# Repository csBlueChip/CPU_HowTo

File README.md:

Ideally:
* Grab a copy of Notepad++
* Load the provided language file
* Read the HowTo

Sub-optimally:
* Read the HowTo without the syntax highlighing

Alternatively:
* Port the language file to your favourite text editor
* `~~~ (  SECTION HEADING  ) =====`<br/>
`~-~ SUBSECTION HEADING ~-~ `<br/>
`(o) DIAGRAM TITLE`<br/>
`! ASCII Art`<br/>
`` `CODE` ``<br/>
`"QUOTED STRING"`<br/>
`<~ SPOILER ~>`<br/>
`{NAME}`<br/>
`!!!ALERT!!!`<br/>

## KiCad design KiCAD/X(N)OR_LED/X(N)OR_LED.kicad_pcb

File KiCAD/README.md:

&nbsp;&nbsp;&nbsp;<br/>
&nbsp;&nbsp;&nbsp;<br/>

&nbsp;&nbsp;&nbsp;<br/>

&nbsp;&nbsp;&nbsp;<br/>
&nbsp;&nbsp;&nbsp;<br/>

&nbsp;&nbsp;&nbsp;<br/>

&nbsp;&nbsp;&nbsp;<br/>
&nbsp;&nbsp;&nbsp;<br/>
&nbsp;&nbsp;&nbsp;<br/>
&nbsp;&nbsp;&nbsp;<br/>

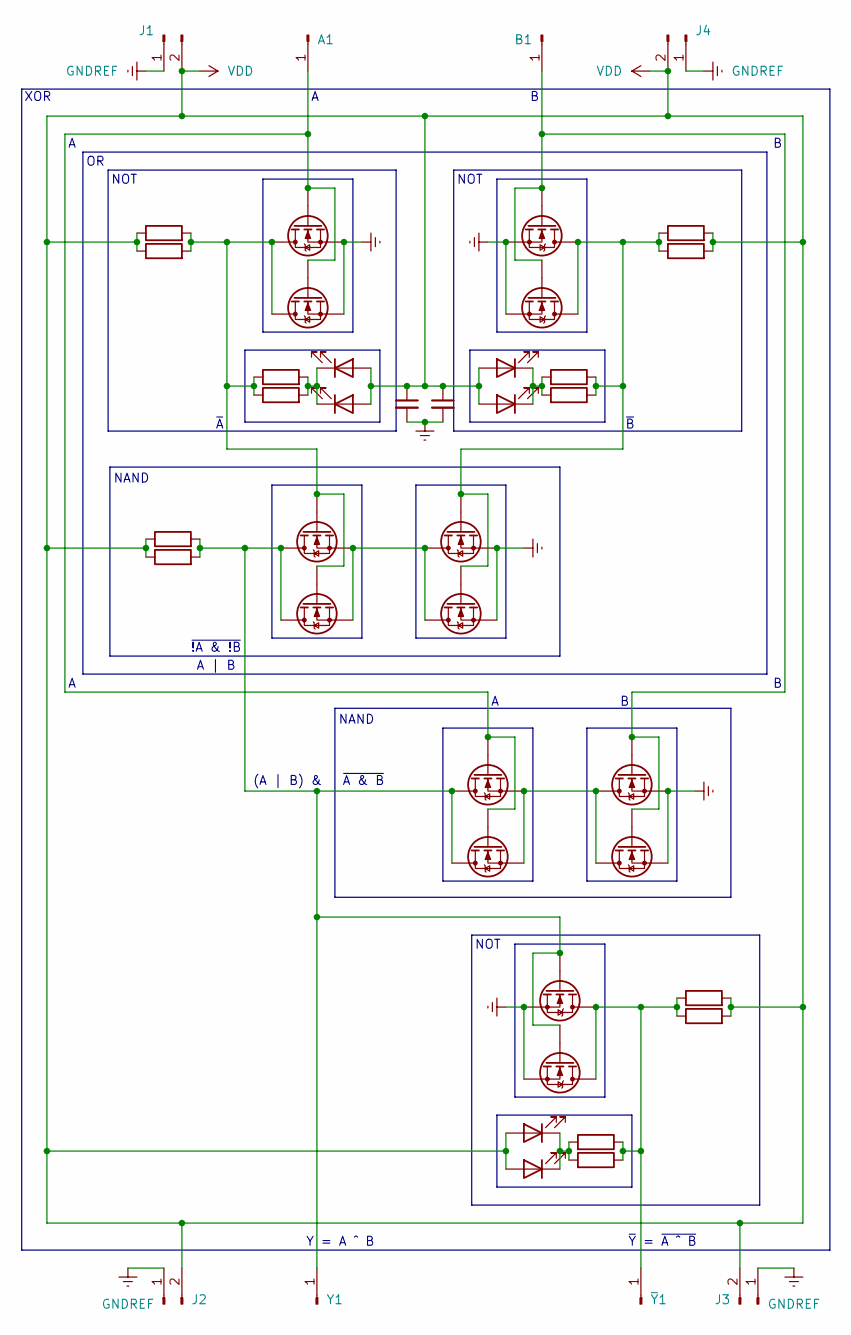
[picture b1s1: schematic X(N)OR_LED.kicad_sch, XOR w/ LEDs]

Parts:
A1: Conn_01x01_Pin; PinHeader_1x01_P2.54mm_Vertical
B1: Conn_01x01_Pin; PinHeader_1x01_P2.54mm_Vertical
C1: C_Small; C_Disc_D3.0mm_W2.0mm_P2.50mm
C2: C_Small; C_1206_3216Metric_Pad1.33x1.80mm_HandSolder
D1, D2, D3: LED; LED_D1.8mm_W3.3mm_H2.4mm
D11, D12, D13: LED; LED_1206_3216Metric
J1, J2, J3, J4: Conn_01x02_Pin; PinSocket_1x02_P2.54mm_Vertical
Q1, Q2, Q3, Q4, Q5, Q6, Q7: 2N7000; TO-92_Inline
Q11, Q12, Q13, Q14, Q15, Q16, Q17: 2N7000; SOT-23
R1, R2, R3, R4, R5, R6, R7: R; R_Axial_DIN0207_L6.3mm_D2.5mm_P10.16mm_Horizontal
R11, R12, R13, R14, R15, R16, R17: R; R_1206_3216Metric
Y1: Conn_01x01_Pin; PinHeader_1x01_P2.54mm_Vertical
~{Y}1: Conn_01x01_Pin; PinHeader_1x01_P2.54mm_Vertical

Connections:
GNDREF: C1.2, C2.2, J1.1, J2.1, J3.1, J4.1, Q1.1 (S), Q2.1 (S), Q4.1 (S), Q6.1 (S), Q7.1 (S), Q11.1 (S), Q12.1 (S), Q14.1 (S), Q16.1 (S), Q17.1 (S)
unnamed: A1.1, Q1.2 (G), Q5.2 (G), Q11.2 (G), Q15.2 (G)
unnamed: B1.1, Q2.2 (G), Q6.2 (G), Q12.2 (G), Q16.2 (G)
unnamed: D1.1 (K), D11.1 (K), R3.2, R13.2
unnamed: D2.1 (K), D12.1 (K), R4.2, R14.2
unnamed: D3.1 (K), D13.1 (K), R7.2, R17.2
unnamed: Q1.3 (D), Q3.2 (G), Q11.3 (D), Q13.2 (G), R1.2, R3.1, R11.2, R13.1
unnamed: Q2.3 (D), Q4.2 (G), Q12.3 (D), Q14.2 (G), R2.1, R4.1, R12.1, R14.1
unnamed: Q3.3 (D), Q5.3 (D), Q7.2 (G), Q13.3 (D), Q15.3 (D), Q17.2 (G), R5.2, R15.2, Y1.1
unnamed: Q3.1 (S), Q4.3 (D), Q13.1 (S), Q14.3 (D)
unnamed: Q5.1 (S), Q6.3 (D), Q15.1 (S), Q16.3 (D)
unnamed: Q7.3 (D), Q17.3 (D), R6.1, R7.1, R16.1, R17.1, ~{Y}1.1
VDD: C1.1, C2.1, D1.2 (A), D2.2 (A), D3.2 (A), D11.2 (A), D12.2 (A), D13.2 (A), J1.2, J2.2, J3.2, J4.2, R1.1, R2.2, R5.1, R6.2, R11.1, R12.2, R15.1, R16.2

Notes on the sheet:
NOT
~{Y} = ~{A ^ B}
XOR
~{A}
~{!A & !B}
A | B
NAND
Y = A ^ B
~{B}
(A | B) & ~{A & B}

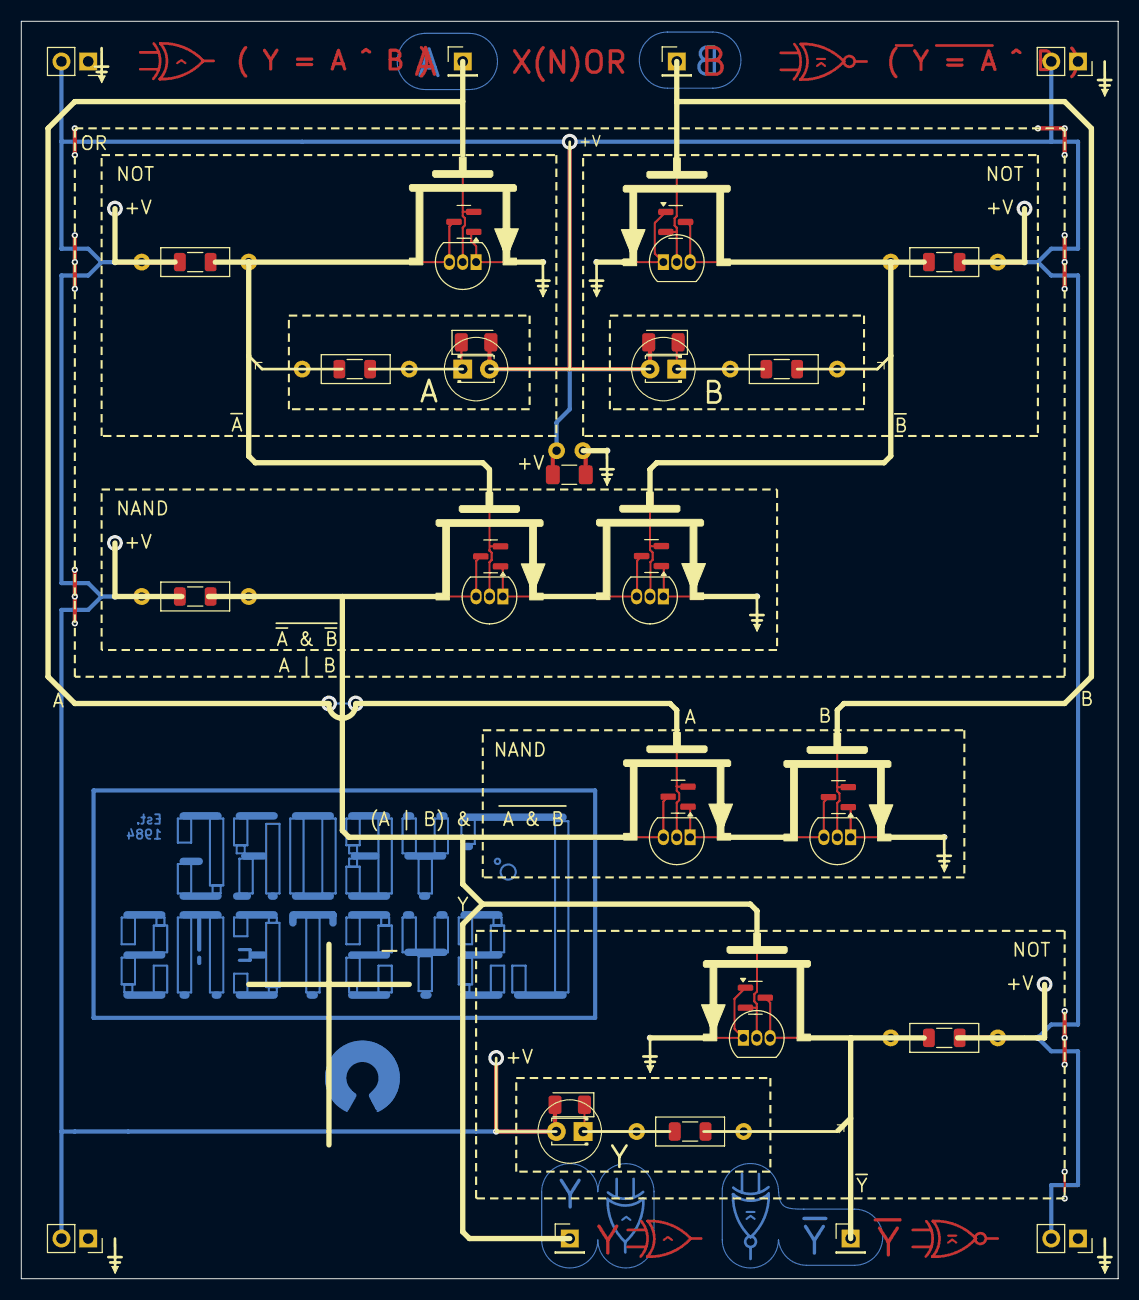
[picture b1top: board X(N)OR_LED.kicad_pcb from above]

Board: 2 copper layers, 104.1 x 119.4 mm, 43 parts (0 on the bottom side), 13 nets.

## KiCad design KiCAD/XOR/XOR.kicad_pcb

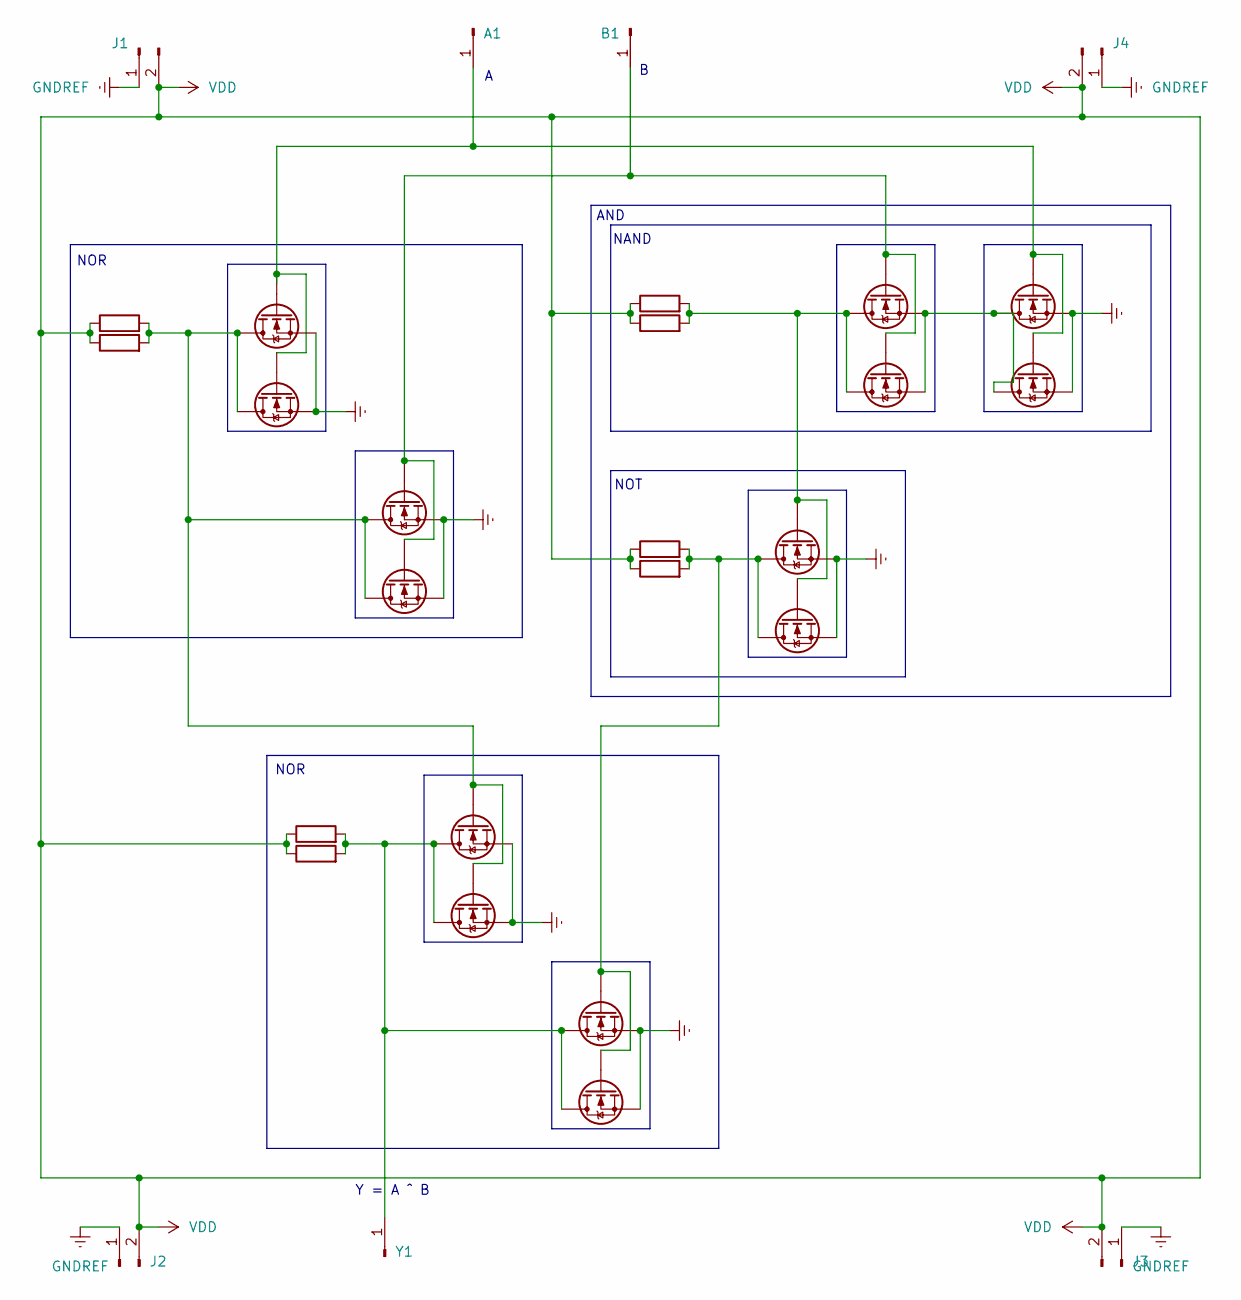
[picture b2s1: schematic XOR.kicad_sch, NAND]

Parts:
A1: Conn_01x01_Pin; PinHeader_1x01_P2.54mm_Vertical
B1: Conn_01x01_Pin; PinHeader_1x01_P2.54mm_Vertical
J1, J2, J3, J4: Conn_01x02_Pin; PinSocket_1x02_P2.54mm_Vertical
Q5, Q6, Q7, Q8, Q9, Q10, Q11: 2N7000; TO-92_Inline
Q15, Q16, Q17, Q18, Q19, Q20, Q21: 2N7000; SOT-23
R6, R7, R8, R9: R; R_Axial_DIN0207_L6.3mm_D2.5mm_P10.16mm_Horizontal
R16, R17, R18, R19: R; R_1206_3216Metric
Y1: Conn_01x01_Pin; PinHeader_1x01_P2.54mm_Vertical

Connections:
GNDREF: J1.1, J2.1, J3.1, J4.1, Q5.1 (S), Q6.1 (S), Q7.1 (S), Q8.1 (S), Q10.1 (S), Q11.1 (S), Q15.1 (S), Q16.1 (S), Q17.1 (S), Q18.1 (S), Q20.1 (S), Q21.1 (S)
unnamed: A1.1, Q5.2 (G), Q10.2 (G), Q15.2 (G), Q20.2 (G)
unnamed: B1.1, Q6.2 (G), Q9.2 (G), Q16.2 (G), Q19.2 (G)
unnamed: Q9.1 (S), Q10.3 (D), Q19.1 (S), Q20.3 (D)
unnamed: Q8.2 (G), Q11.3 (D), Q18.2 (G), Q21.3 (D), R9.2, R19.2
unnamed: Q9.3 (D), Q11.2 (G), Q19.3 (D), Q21.2 (G), R8.2, R18.2
unnamed: Q5.3 (D), Q6.3 (D), Q7.2 (G), Q15.3 (D), Q16.3 (D), Q17.2 (G), R6.2, R16.2
unnamed: Q7.3 (D), Q8.3 (D), Q17.3 (D), Q18.3 (D), R7.2, R17.2, Y1.1
VDD: J1.2, J2.2, J3.2, J4.2, R6.1, R7.1, R8.1, R9.1, R16.1, R17.1, R18.1, R19.1

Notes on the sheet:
NOR
AND
NAND
Y = A ^ B
NOT

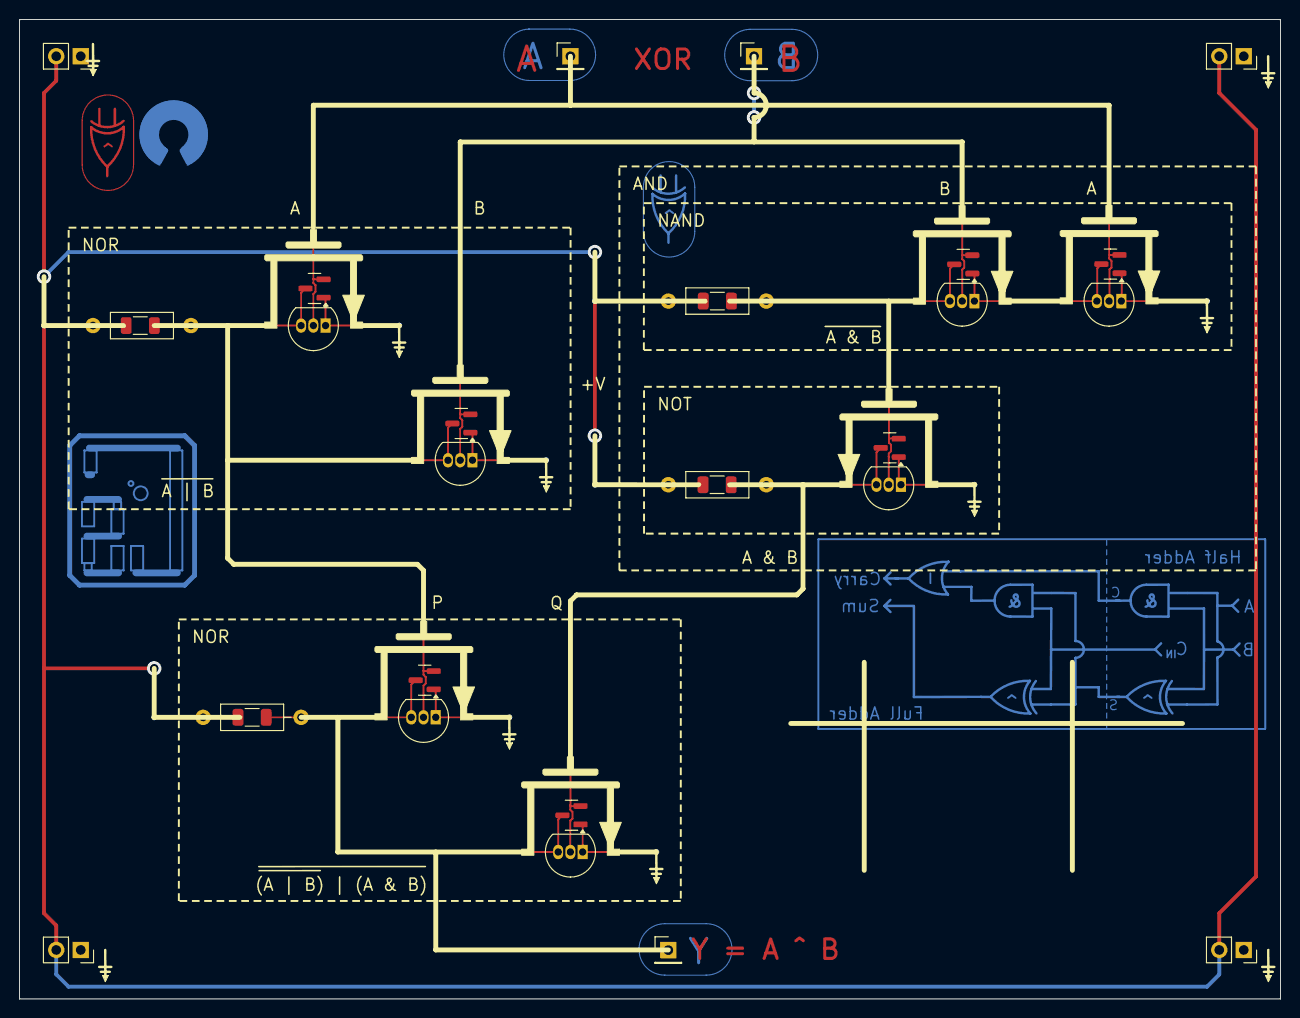
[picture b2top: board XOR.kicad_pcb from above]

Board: 2 copper layers, 130.8 x 101.6 mm, 29 parts (0 on the bottom side), 9 nets.

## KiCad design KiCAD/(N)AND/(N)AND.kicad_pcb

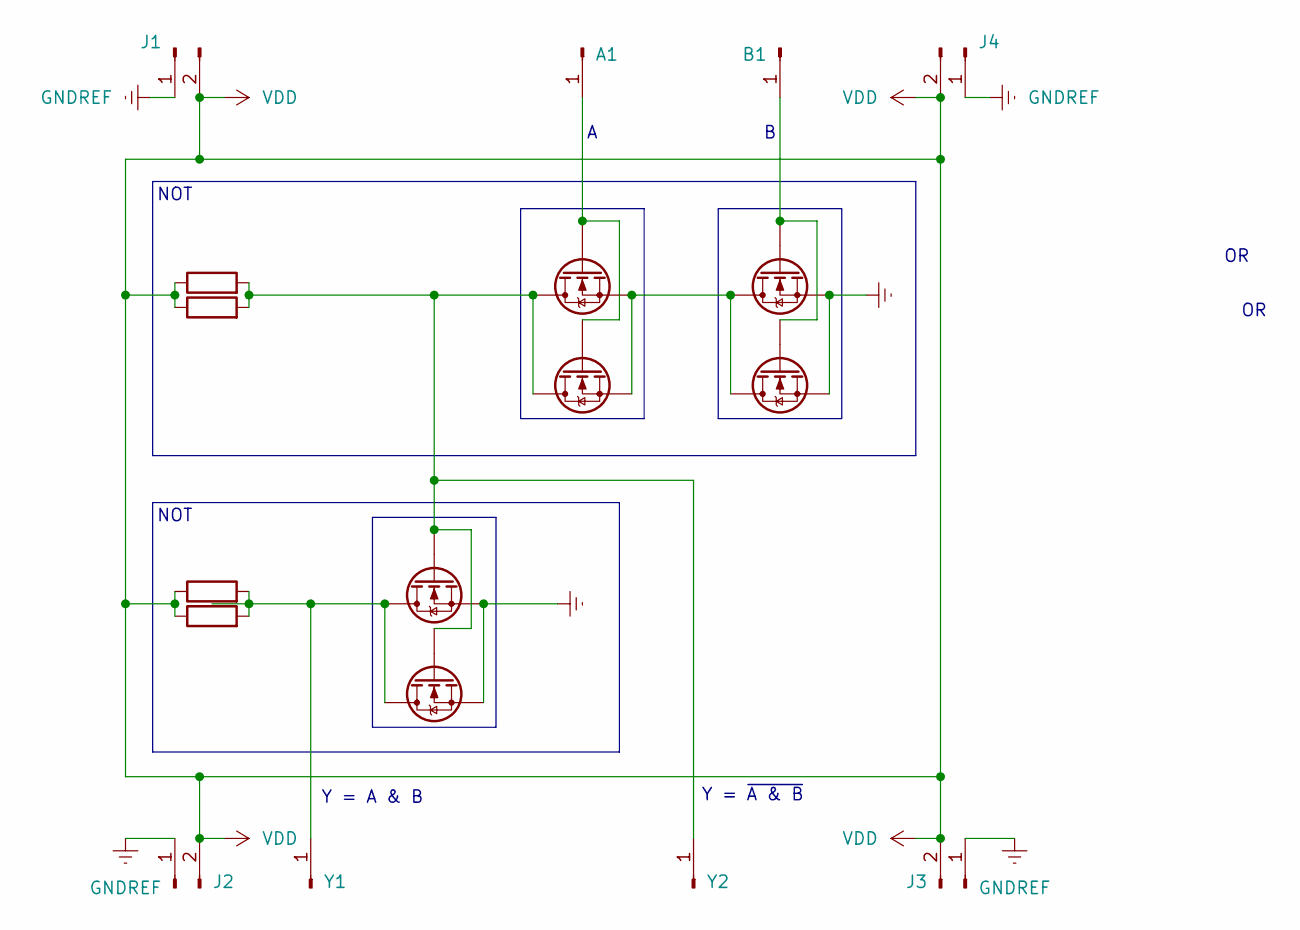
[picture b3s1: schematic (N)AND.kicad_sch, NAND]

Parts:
A1: Conn_01x01_Pin; PinHeader_1x01_P2.54mm_Vertical
B1: Conn_01x01_Pin; PinHeader_1x01_P2.54mm_Vertical
J1, J2, J3, J4: Conn_01x02_Pin; PinSocket_1x02_P2.54mm_Vertical
Q3, Q4, Q5: 2N7000; TO-92_Inline
Q13, Q14, Q15: 2N7000; SOT-23
R5, R6: R; R_Axial_DIN0207_L6.3mm_D2.5mm_P10.16mm_Horizontal
R15, R16: R; R_1206_3216Metric
Y1, Y2: Conn_01x01_Pin; PinHeader_1x01_P2.54mm_Vertical

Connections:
GNDREF: J1.1, J2.1, J3.1, J4.1, Q4.1 (S), Q5.1 (S), Q14.1 (S), Q15.1 (S)
unnamed: A1.1, Q3.2 (G), Q13.2 (G)
unnamed: B1.1, Q4.2 (G), Q14.2 (G)
unnamed: Q3.3 (D), Q5.2 (G), Q13.3 (D), Q15.2 (G), R5.2, R15.2, Y2.1
unnamed: Q3.1 (S), Q4.3 (D), Q13.1 (S), Q14.3 (D)
unnamed: Q5.3 (D), Q15.3 (D), R6.2, R16.2, Y1.1
VDD: J1.2, J2.2, J3.2, J4.2, R5.1, R6.1, R15.1, R16.1

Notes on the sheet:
NOT
Y = ~{A & B}
Y = A & B

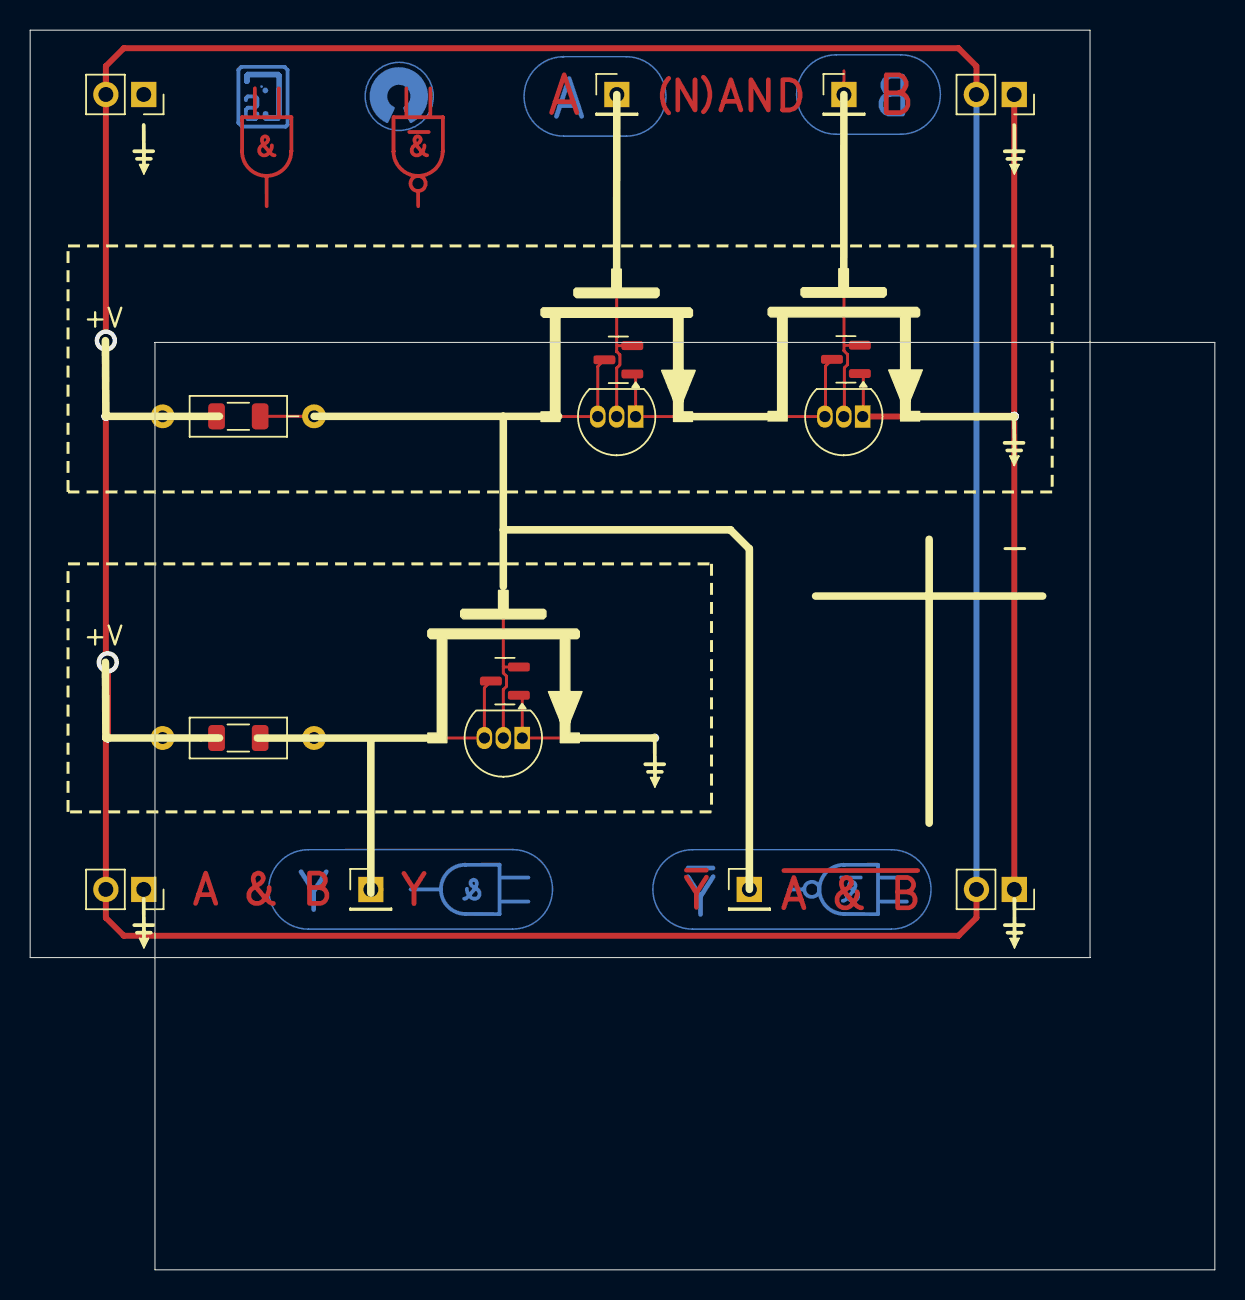
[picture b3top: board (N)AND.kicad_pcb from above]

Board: 2 copper layers, 79.5 x 83.2 mm, 18 parts (0 on the bottom side), 7 nets.

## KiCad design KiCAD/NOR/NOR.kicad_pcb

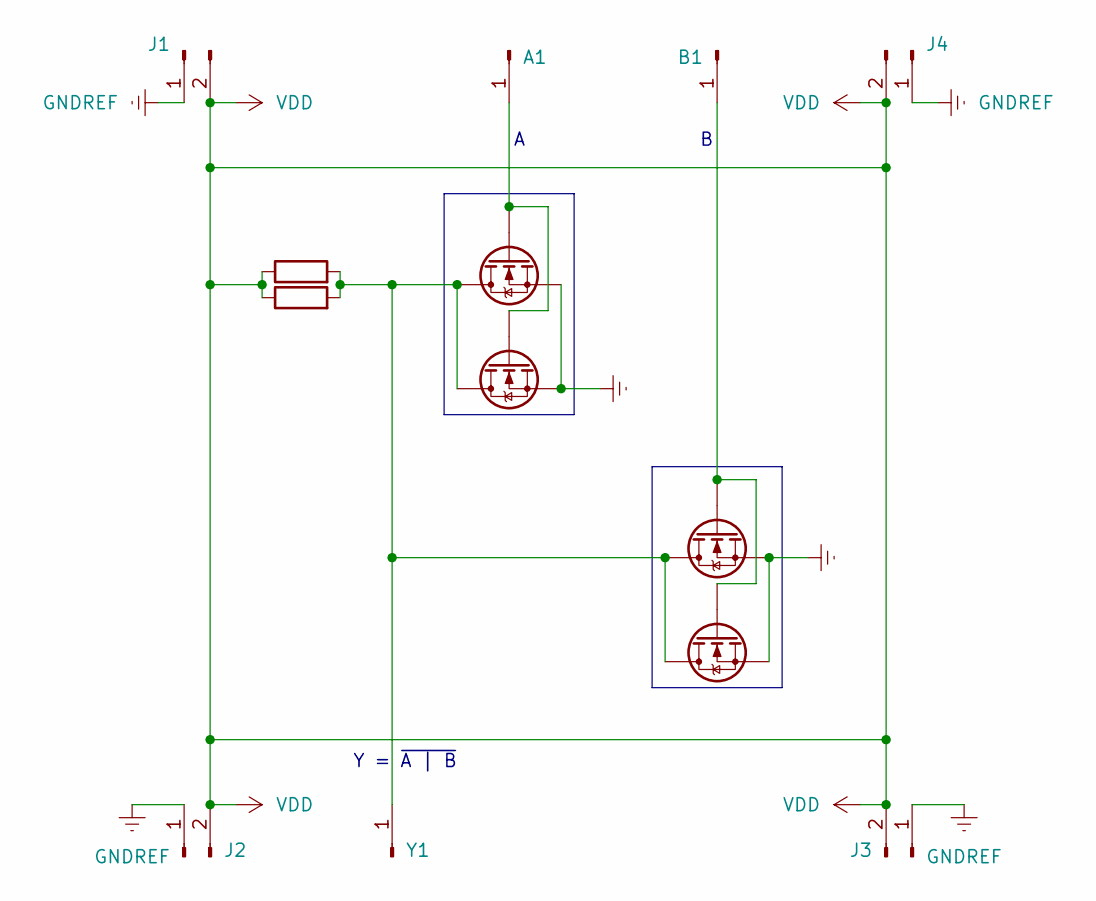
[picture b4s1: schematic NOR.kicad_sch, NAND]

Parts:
A1: Conn_01x01_Pin; PinHeader_1x01_P2.54mm_Vertical
B1: Conn_01x01_Pin; PinHeader_1x01_P2.54mm_Vertical
J1, J2, J3, J4: Conn_01x02_Pin; PinSocket_1x02_P2.54mm_Vertical
Q3, Q4: 2N7000; TO-92_Inline
Q13, Q14: 2N7000; SOT-23
R5: R; R_Axial_DIN0207_L6.3mm_D2.5mm_P10.16mm_Horizontal
R15: R; R_1206_3216Metric
Y1: Conn_01x01_Pin; PinHeader_1x01_P2.54mm_Vertical

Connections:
GNDREF: J1.1, J2.1, J3.1, J4.1, Q3.1 (S), Q4.1 (S), Q13.1 (S), Q14.1 (S)
unnamed: A1.1, Q3.2 (G), Q13.2 (G)
unnamed: B1.1, Q4.2 (G), Q14.2 (G)
unnamed: Q3.3 (D), Q4.3 (D), Q13.3 (D), Q14.3 (D), R5.2, R15.2, Y1.1
VDD: J1.2, J2.2, J3.2, J4.2, R5.1, R15.1

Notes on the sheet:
Y = ~{A | B}

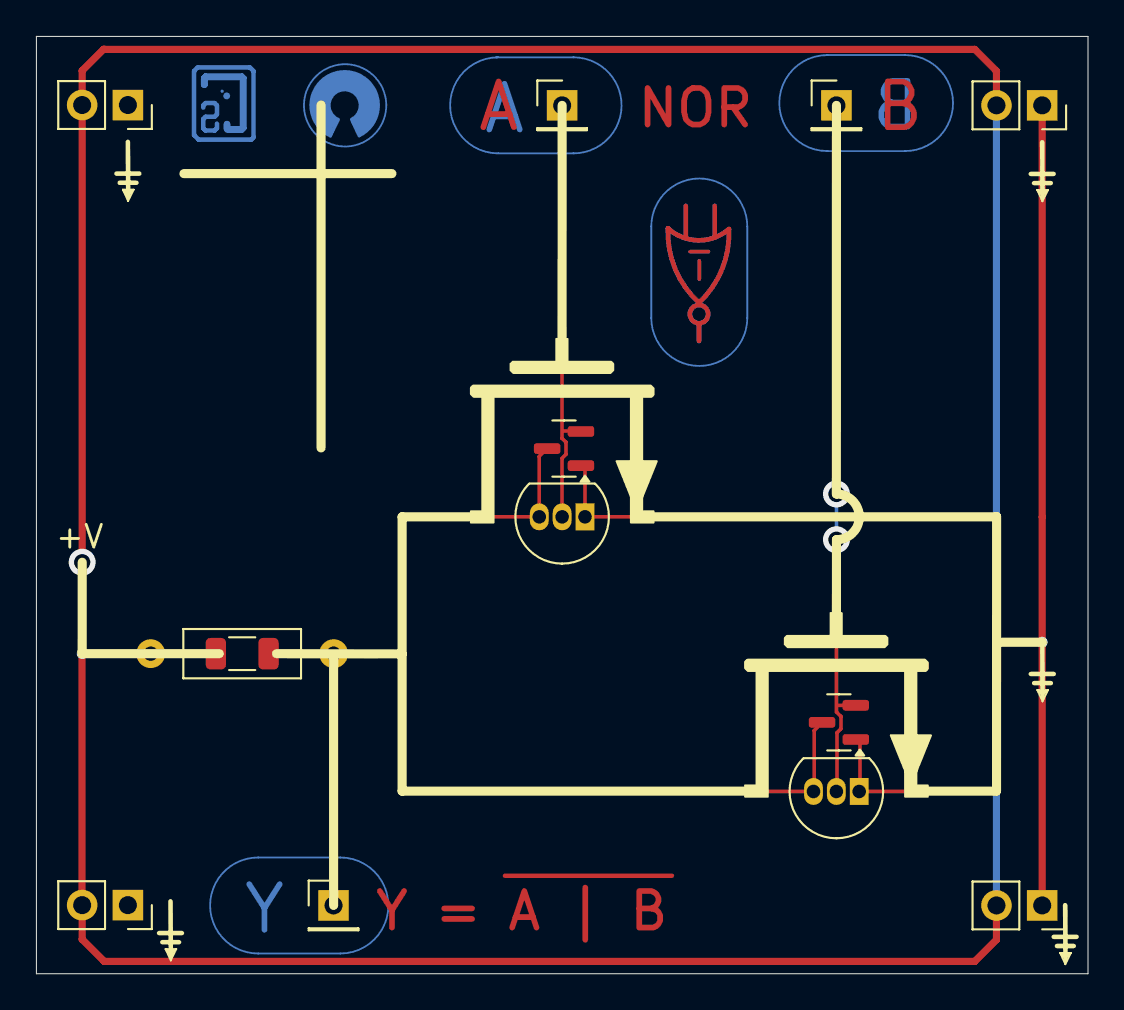
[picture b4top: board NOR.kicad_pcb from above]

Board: 2 copper layers, 58.4 x 52.1 mm, 13 parts (0 on the bottom side), 5 nets.

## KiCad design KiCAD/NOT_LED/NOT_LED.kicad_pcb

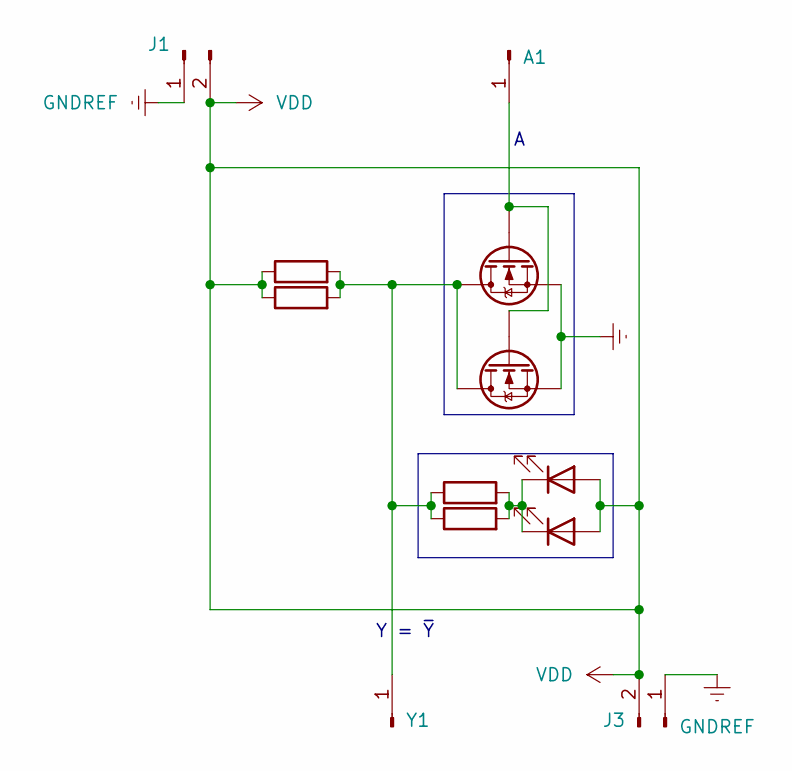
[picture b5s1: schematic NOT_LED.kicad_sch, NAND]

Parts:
A1: Conn_01x01_Pin; PinHeader_1x01_P2.54mm_Vertical
D1: LED; LED_D1.8mm_W3.3mm_H2.4mm
D11: LED; LED_1206_3216Metric
J1, J3: Conn_01x02_Pin; PinSocket_1x02_P2.54mm_Vertical
Q3: 2N7000; TO-92_Inline
Q13: 2N7000; SOT-23
R3, R5: R; R_Axial_DIN0207_L6.3mm_D2.5mm_P10.16mm_Horizontal
R13, R15: R; R_1206_3216Metric
Y1: Conn_01x01_Pin; PinHeader_1x01_P2.54mm_Vertical

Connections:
GNDREF: J1.1, J3.1, Q3.1 (S), Q13.1 (S); also elsewhere on the board
unnamed: A1.1, Q3.2 (G), Q13.2 (G)
unnamed: D1.1 (K), D11.1 (K), R3.2, R13.2
unnamed: Q3.3 (D), Q13.3 (D), R3.1, R5.2, R13.1, R15.2, Y1.1
VDD: D1.2 (A), D11.2 (A), J1.2, J3.2, R5.1, R15.1; also elsewhere on the board

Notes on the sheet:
Y = ~{Y}

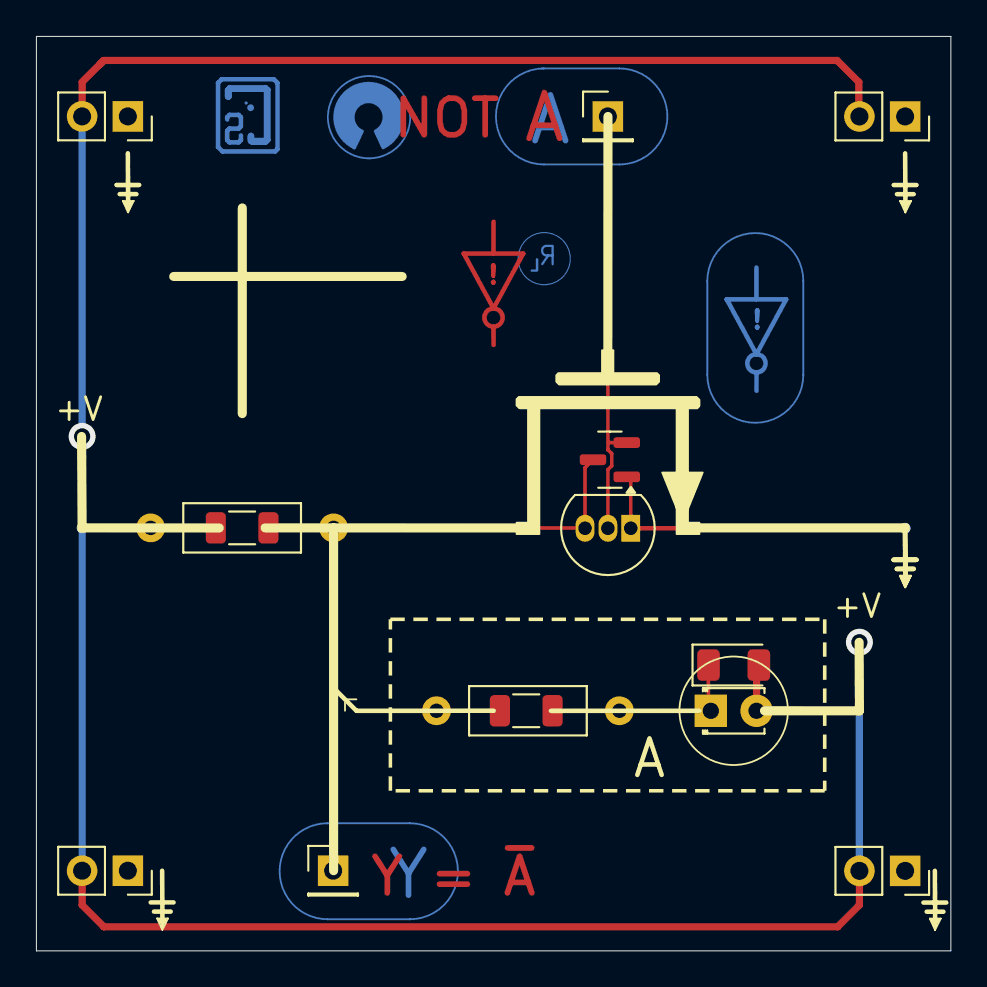
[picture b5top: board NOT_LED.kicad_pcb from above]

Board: 2 copper layers, 50.8 x 50.8 mm, 14 parts (0 on the bottom side), 5 nets.

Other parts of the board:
J2, J4: Conn_01x02_Pin; PinSocket_1x02_P2.54mm_Vertical

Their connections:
GNDREF: J2.1, J4.1; also elsewhere on the board
VDD: J2.2, J4.2; also elsewhere on the board

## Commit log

2025-04-21 Initial Commit # Gimp : Art template # Falstad : Gate & Bus diagrams # KiCAD v9 : NAND, NOR, NOT, X(N)OR
2025-04-21 KiCAD: (N)AND
2025-04-22 Cleanup
2025-04-24 (N)OR
2025-04-24 Rename X(N)OR_LED
2025-04-24 (N)OR_LED
2025-04-25 KiCAD: NOT_LED
2025-04-25 KiCAD: (N)AND_LED
2025-04-27 KiCAD: XOR
2025-04-27 Create README.md
    pics
2025-04-27 typo
2025-04-27 docs
2025-05-06 Howto document

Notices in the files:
KiCAD/NOR/NOR.kicad_pcb:
Copyright BlueChip 2025.
This source describes Open Hardware and is licensed
under the CERN-OHL-P v2
and make products using it under the terms of the
CERN-OHL-P v2 (https:/cern.ch/cern-ohl).
KiCAD/X(N)OR_LED/X(N)OR_LED.kicad_pcb:
Licence:
CERN-OSH-P-2.0
